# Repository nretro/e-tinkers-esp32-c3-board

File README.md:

# USB_JTAG mod of E-Tinkers ESP32-C3 Board

The ESP32-C3 chip has a USB to JTAG bridge built in, but no dev board directly makes use of it. So I modified

The main differences are:
  * micro USB connector with ESD protection (CM1231)
  * different LDO (TLV76733DRVR)
  * removed the flash button (not needed when using JTAG)
  * modified some footprints:
	* all necessary resistors and capacitors have 0805 footprints, which also allows to use 0603 parts
	* deleted the antenna from the module footprint since that interferes with panelizing 
	* stretched pads of the WS2812 footprint to aid hand soldering

Options:
  * added optional 22pF capacitors to D+ and D- lines on the bottom. They appear on the schematics of the official dev board, but seem not to be necessary.
  * populating R4 with a 0 ohm resistor will connect USB shield with GND. Usually shield is connected to GND at the host and not at devices downstream. Therefore R4 should be left unpopulated in most applications. 
  * the LDO can be disabled by connecting LDO_EN to GND to save energy when not used.

Please note that since I made some minor modifications after receiving
the first patch of PCBs, I have not yet used the gerbers in the
archive to fabricate actual boards. Therefore there is a small chance
that those contain errors.

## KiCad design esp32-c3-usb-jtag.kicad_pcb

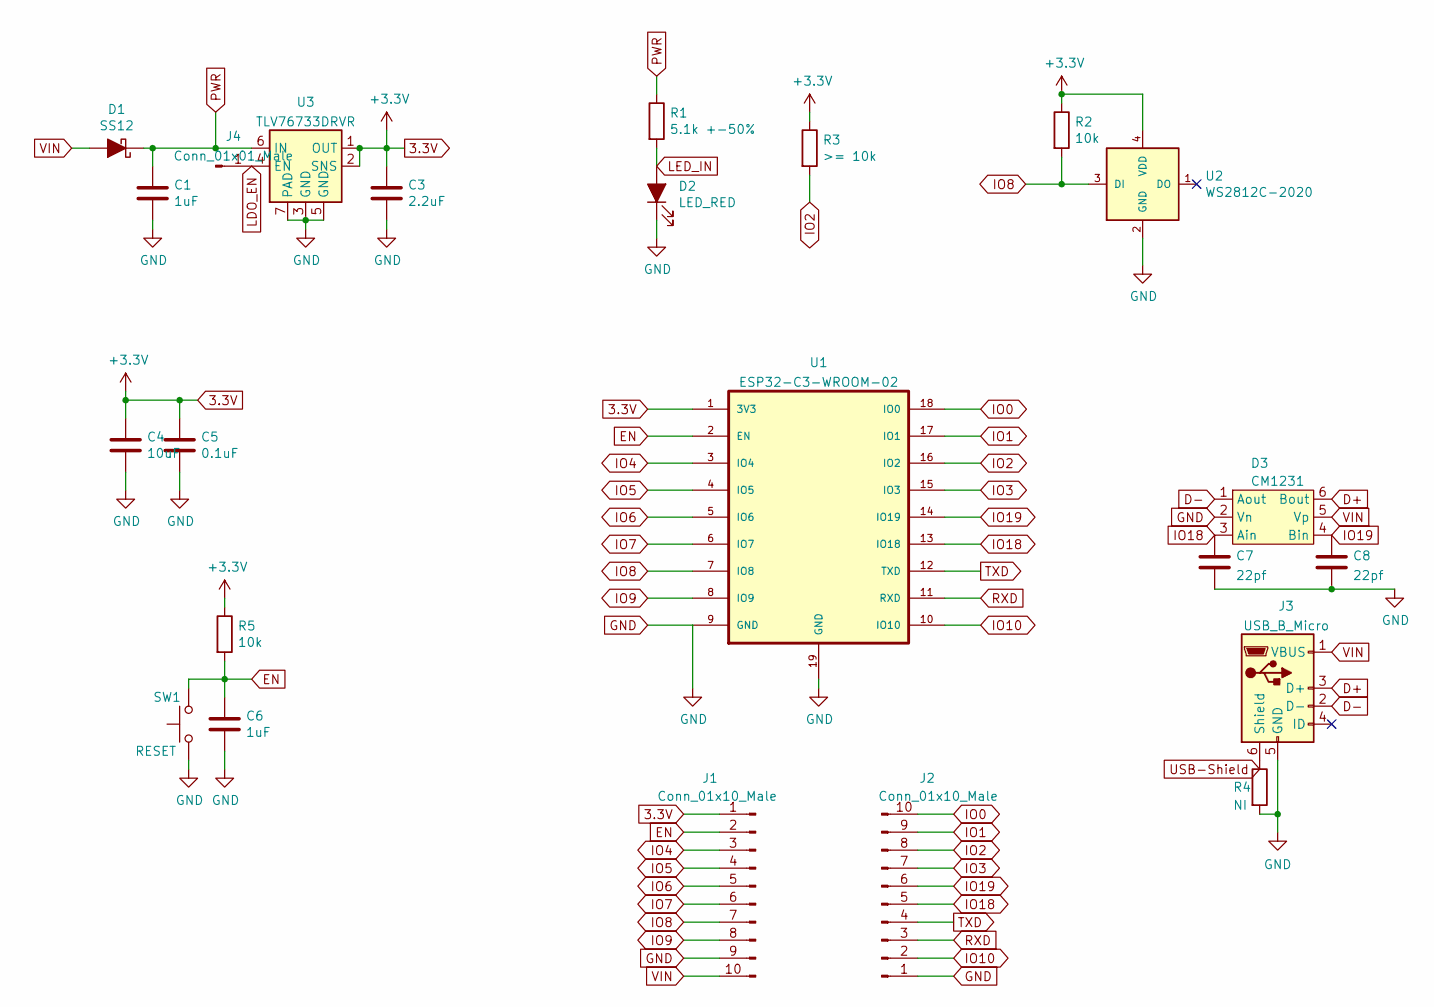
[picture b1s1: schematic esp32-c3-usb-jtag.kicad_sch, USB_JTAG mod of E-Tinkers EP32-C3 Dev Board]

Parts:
C1, C6: 1uF; C_0805_2012Metric
C3: 2.2uF; C_0805_2012Metric
C4: 10uF; C_0805_2012Metric
C5: 0.1uF; C_0805_2012Metric
C7, C8: 22pf; C_0603_1608Metric
D1: SS12; D_SMA
D2: LED_RED; LED_0805_2012Metric
D3: CM1231; SOT-23-6_Handsoldering
J1, J2: Conn_01x10_Male; PinHeader_1x10_P2.54mm_Vertical
J3: USB_B_Micro; USB_Micro-B_China
J4: Conn_01x01_Male; PinHeader_1x01_P2.54mm_Vertical
R1: 5.1k +-50%; R_0603_1608Metric_Pad1.05x0.95mm_HandSolder
R2, R5: 10k; R_0603_1608Metric_Pad1.05x0.95mm_HandSolder
R3: >= 10k; R_0603_1608Metric_Pad1.05x0.95mm_HandSolder
R4: NI; R_0603_1608Metric
SW1: RESET; SW_TS-1185-X-X
U1: ESP32-C3-WROOM-02; ESP32-C3-WROOM-02_ant
U2: WS2812C-2020; LED_WS2812C-2020_hand
U3: TLV76733DRVR; WSON-6-1EP_2x2mm_P0.65mm_EP1x1.6mm_ThermalVias

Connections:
3.3V: C3.1, C4.1, C5.1, J1.1, R2.1, R3.1, R5.1, U1.1 (3V3), U2.4 (VDD), U3.1 (OUT), U3.2 (SNS)
D+: D3.6 (Bout), J3.3 (D+)
D-: D3.1 (Aout), J3.2 (D-)
EN: C6.1, J1.2, R5.2, SW1.2, U1.2 (EN)
GND: C1.2, C3.2, C4.2, C5.2, C6.2, C7.2, C8.2, D2.1 (K), D3.2 (Vn), J1.9, J2.1, J3.5 (GND), R4.2, SW1.1, U1.9 (GND), U1.19 (GND), U2.2 (GND), U3.3 (GND), U3.5 (GND), U3.7 (PAD)
IO0: J2.10, U1.18 (IO0)
IO1: J2.9, U1.17 (IO1)
IO2: J2.8, R3.2, U1.16 (IO2)
IO3: J2.7, U1.15 (IO3)
IO4: J1.3, U1.3 (IO4)
IO5: J1.4, U1.4 (IO5)
IO6: J1.5, U1.5 (IO6)
IO7: J1.6, U1.6 (IO7)
IO8: J1.7, R2.2, U1.7 (IO8), U2.3 (DI)
IO9: J1.8, U1.8 (IO9)
IO10: J2.2, U1.10 (IO10)
IO18: C7.1, D3.3 (Ain), J2.5, U1.13 (IO18)
IO19: C8.1, D3.4 (Bin), J2.6, U1.14 (IO19)
LDO_EN: J4.1, U3.4 (EN)
LED_IN: D2.2 (A), R1.2
unnamed: J3.6 (Shield), R4.1
PWR: C1.1, D1.1 (K), R1.1, U3.6 (IN)
RXD: J2.3, U1.11 (RXD)
TXD: J2.4, U1.12 (TXD)
VIN: D1.2 (A), D3.5 (Vp), J1.10, J3.1 (VBUS)

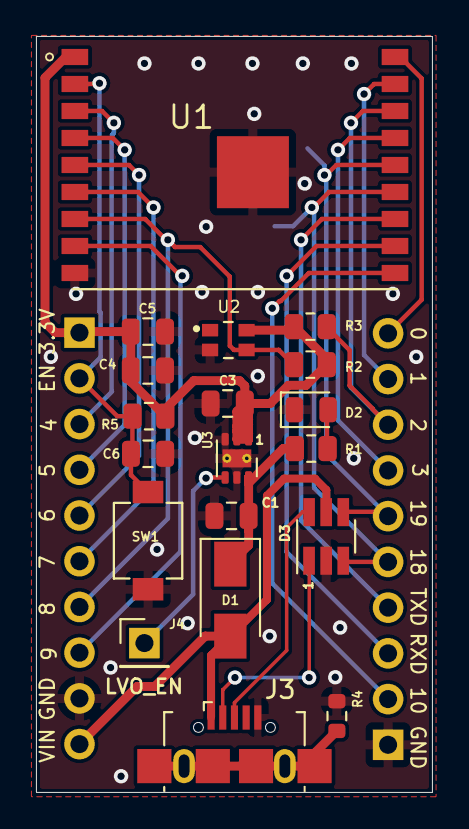
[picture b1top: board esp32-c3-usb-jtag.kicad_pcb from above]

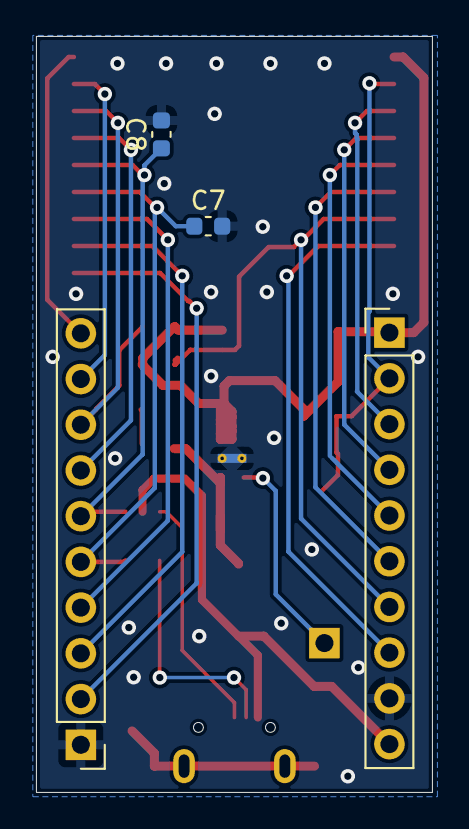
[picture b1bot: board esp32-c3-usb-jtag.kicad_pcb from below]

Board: 2 copper layers, 22.0 x 42.0 mm, 23 parts (4 on the bottom side), 25 nets.

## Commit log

2022-02-19 USB_JTAG mod
